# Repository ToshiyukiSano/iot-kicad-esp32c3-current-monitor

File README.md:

# 生成AI × KiCadで始めるIoTハードウェア開発

**マイコン・センサー・回路図・PCB・ファームウェアを、生成AIと協働して試作するための実践ノート。**

> **ステータス（2026-11-01）：設計デモ / 未実機検証**
> KiCad 10.0.8での回路図作成、PCB配線、ERC/DRCチェックはClaude Codeの作業報告上で完了。一方、計測ファームウェアのコンパイル・実機動作、測定精度、電源OFF時の保護、CT開放時の安全性は未確認です。**製造・工作機械への設置を許可する資料ではありません。**

## このリポジトリで学べること

- Arduino/ESP32などのマイコンとセンサーから、IoT装置の要件を整理する
- **Claude Code + KiCad MCP + KiCad 10** をUbuntuで使う
- AIで回路図を生成しても、**データシート・ERC・ネットリスト・実物のピン配置で検証する**
- シンボル・フットプリントの作成、PCBの部品配置・配線・GNDベタ・DRCまで進める
- ADCのサンプリング、RMS計算、校正、Wi-Fi送信を段階的に実装する
- 再コンパイルによるフットプリント消失など、実際に遭遇した失敗を避ける

## 実例：工作機械向け電流モニター

今回のケーススタディは、**Seeed Studio XIAO ESP32C3 + SR-3704-150N（分割型CT）**による1チャンネル交流電流モニターです。工作機械の加工負荷変化を、電流の時系列として記録することを目標にしています。

**注：** 上の画像はKiCadから書き出されたPCBの可視化であり、製造した実物や通電試験の結果ではありません。XIAO本体・ソケットは画像に含まれません。

| 区分 | 設計・目標値 | 検証状態 |
|---|---|---|
| マイコン | XIAO ESP32C3 / A1 = GPIO3（ADC1） | ピン割当は公式資料と照合したとの報告 |
| センサー | SR-3704-150N、50/60Hz、変流比3000:1、～80A | メーカー納入仕様書を確認 |
| CT負担抵抗 | 10Ω / 1% / 1/4W | 回路上に配置、実測未実施 |
| バイアス | 約1.65V（10kΩ × 2、10µF） | 設計値のみ |
| ADC前段 | 4.7kΩ＋100nF（理論 fc ≒339Hz）、BAT54S | 設計値のみ／保護未検証 |
| 処理 | 約2kサンプル/秒、0.2秒ごとにRMS | **目標**。実機タイミング未検証 |
| PCB | 2層、50×40mm、板厚1.6mm、35µm銅 | KiCad DRC 0件との報告 |
| 通信 | Wi-Fiで記録・可視化 | 将来予定・未実装／未検証 |

## 読み進め方

| 章 | 内容 |
|---|---|
| [01 要件・システム設計](docs/01-system-design.md) | 目的、マイコンの選び方、データフロー |
| [02 開発環境](docs/02-environment.md) | Ubuntu、KiCad、Claude Code、MCP |
| [03 回路設計・部品選定](docs/03-circuit-design.md) | CT、ADC、保護、測定原理 |
| [04 KiCad回路図からPCB](docs/04-kicad-workflow.md) | ERC、フットプリント、配線、DRC、3D |
| [05 計測ファームウェア](docs/05-firmware.md) | サンプリング、RMS、校正、ログ |
| [06 試作・検証計画](docs/06-testing.md) | 低電圧での試験、判定、データ記録 |
| [07 安全・未解決事項](docs/07-safety-open-items.md) | 実機接続前の必須確認 |
| [08 AIへの指示と失敗集](docs/08-ai-prompts-and-lessons.md) | 再利用可能なプロンプト、対処法 |
| [09 GitHub公開手順](docs/09-publishing.md) | ソース移管と公開手順 |
| [10 PCB製造・PCBAと費用](docs/10-pcba-ordering-and-cost.md) | 業者での部品実装、必要ファイル、5枚試作の概算と発注前確認 |

## この配布物に含まれないもの

この文書セットは、会話中の作業ログをもとに再構成しています。Ubuntu上にClaudeが作った **`current-monitor.kicad_sch`、`.kicad_pcb`、`.ino`、BOM CSV、詳細3Dモデルは、この会話には実ファイルとして提供されていないため同梱していません**。GitHubでソースも公開したいときは [移管スクリプト](scripts/import_local_project.sh) を使用し、元のPCから安全にコピーしてください。

## 主要資料

- [Seeed Studio XIAO ESP32C3公式資料](https://wiki.seeedstudio.com/XIAO_ESP32C3_Getting_Started/)
- [SR-3704-150N 納入仕様書（秋月電子掲載PDF）](https://akizukidenshi.com/goodsaffix/SR-3704-150N_20200619.pdf)
- [KiCad 10 PCB Editor公式ドキュメント](https://docs.kicad.org/10.0/ja/pcbnew/pcbnew.html)
- [Claude Code](https://code.claude.com/docs/en/overview)
- [MCP-Kicad（実例で使用したOSS）](https://github.com/unmateria/MCP-Kicad)

> ⚠️ **安全**：CT二次側を開放して一次側に電流を流さないこと。商用・産業用電源の配電盤内作業は設備管理者と適切な資格・権限を有する担当者に依頼してください。AI生成回路のERC/DRC合格は感電・火災・計測精度の保証にはなりません。詳細は [07](docs/07-safety-open-items.md)。

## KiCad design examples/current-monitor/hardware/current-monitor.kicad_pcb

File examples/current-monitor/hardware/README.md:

# 回路・PCBデータの格納先

Claude CodeがUbuntuで作成した `.kicad_sch`、`.kicad_pcb`、`.kicad_pro`、専用 `.kicad_sym`、`.pretty`、ライブラリテーブル等をコピーする場所です。

**現時点では実ファイルが未提供**のため同梱していません。`scripts/import_local_project.sh` で取り込み、別環境で開けることを確認してください。Gerber/製造データはまだ作らないでください。

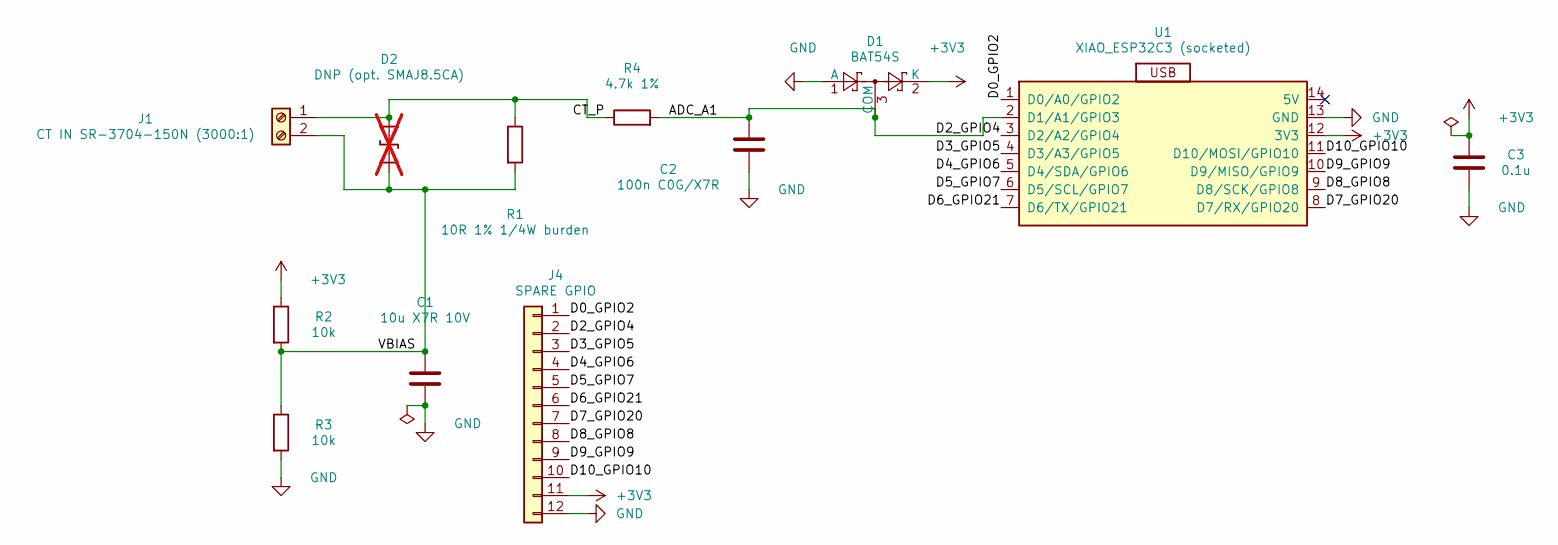
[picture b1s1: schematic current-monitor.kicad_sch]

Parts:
C1: 10u X7R 10V; C_0805_2012Metric
C2: 100n C0G/X7R; C_0805_2012Metric
C3: 0.1u; C_0603_1608Metric
D1: BAT54S; SOT-23
D2: DNP (opt. SMAJ8.5CA); D_SMA; not fitted
J1: CT IN SR-3704-150N (3000:1); TerminalBlock_Phoenix_MKDS-1,5-2-5.08_1x02_P5.08mm_Horizont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
J4: SPARE GPIO; PinHeader_1x12_P2.54mm_Vertical
R1: 10R 1% 1/4W burden; R_1206_3216Metric
R2, R3: 10k; R_0603_1608Metric
R4: 4.7k 1%; R_0603_1608Metric
U1: XIAO_ESP32C3 (socketed); XIAO_ESP32C3_Socket_2x07_P2.54mm_Row15.24mm

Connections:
+3V3: C3.1, D1.2 (K), J4.11, R2.1, U1.12 (3V3)
/ADC_A1: C2.1, D1.3 (COM), R4.2, U1.2 (D1/A1/GPIO3)
/CT_P: D2.1 (A1), J1.1, R1.1, R4.1
/D0_GPIO2: J4.1, U1.1 (D0/A0/GPIO2)
/D2_GPIO4: J4.2, U1.3 (D2/A2/GPIO4)
/D3_GPIO5: J4.3, U1.4 (D3/A3/GPIO5)
/D4_GPIO6: J4.4, U1.5 (D4/SDA/GPIO6)
/D5_GPIO7: J4.5, U1.6 (D5/SCL/GPIO7)
/D6_GPIO21: J4.6, U1.7 (D6/TX/GPIO21)
/D7_GPIO20: J4.7, U1.8 (D7/RX/GPIO20)
/D8_GPIO8: J4.8, U1.9 (D8/SCK/GPIO8)
/D9_GPIO9: J4.9, U1.10 (D9/MISO/GPIO9)
/D10_GPIO10: J4.10, U1.11 (D10/MOSI/GPIO10)
/VBIAS: C1.1, D2.2 (A2), J1.2, R1.2, R2.2, R3.1
GND: C1.2, C2.2, C3.2, D1.1 (A), J4.12, R3.2, U1.13 (GND)

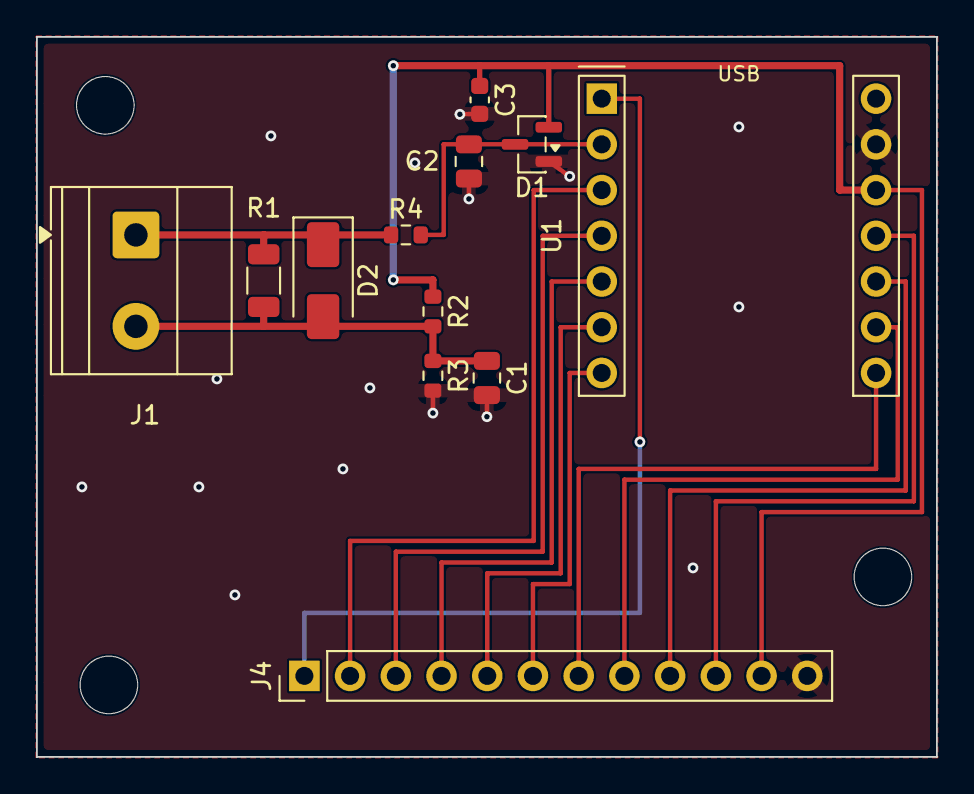
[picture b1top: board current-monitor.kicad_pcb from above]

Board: 2 copper layers, 50.0 x 40.0 mm, 15 parts (0 on the bottom side), 15 nets.

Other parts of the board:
H1, H2, H3: M3; MountingHole_3.2mm_M3
